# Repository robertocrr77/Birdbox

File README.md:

# Birdbox

DIY sensor-triggered ambience player inspired by the [Relaxound Birdybox](https://www.relaxound.com/birdybox-steamed-oak). An ESP32-C6 reads natural birdsong/forest ambience MP3 files from microSD and sends audio to a small speaker through an I2S amplifier. The intended finished device is battery powered; the current prototype is USB powered.

This README consolidates the project history, wiring, firmware behavior, setup, diagnostics, and remaining work. Active source is now V2 in [main/main.c](main/main.c), updated on 2026-11-17. The later V1 wiring/behavior sections describe the previously tested USB prototype and its archived source, not the active V2 image. Build results and physical tests are identified separately.

## Current status

### V2 motherboard routing

The saved two-layer PCB is routed. C1 moved closer to GPIO4. Signal traces
are 0.20 mm, the five supply nets use 0.60–0.80 mm traces, and B.Cu has a
ground pour with thermal reliefs. KiCad DRC and schematic parity reported
zero violations, zero unconnected pads, and zero schematic differences.
Assembly and electrical acceptance checks remain pending.

### Two-pole master switch

SW1 is one external latching DPDT pushbutton. Four individual wires solder
to two separate pairs of motherboard through-holes. Use the pin numbering
from the continuity-tested switch drawing.

| Motherboard pad | Net | Switch pin |
| --- | --- | --- |
| J5.1 | TP4056 protected OUT+ | 1 |
| J5.2 | XL63020 VIN | 2 |
| J7.1 | XL63020 VOUT | 4 |
| J7.2 | +3V3_AON | 5 |

ON closes 1–2 and 4–5. OFF connects 2–3 and 5–6 on the switch; pins 3 and 6
have no wires. Set SW1 to OFF when charging or flashing over the ESP32's USB
port. This opens both the battery feed and the connection between the
XL63020 output and the USB-powered 3.3 V rail. System ground remains common.
The switch's DC current rating and assembled behavior still need verification.

### V2 light sensing and deep sleep — 2026-11-17

Active firmware is `FW=birdbox-v2-light`. It implements motion wake, switched
peripheral power, a photoresistor night inhibit and RTC playlist retention.
**Do not flash onto unchanged V1 wiring:** PIR is now GPIO0; GPIO22 drives Q2.
GPIO4 reads light and GPIO14 excites the divider. Both added pins were checked
against the official Waveshare pinout image (`resources/esp32-c6-pinout.webp`).

Added R5 47k and C1 100n, plus J6 for a cabled bare LDR (R6, excluded from PCB).
J6 pin 1 is LIGHT_ADC_GPIO4; pin 2 is GND. Divider: GPIO14 -> 47k -> GPIO4
-> LDR -> GND, with 100n from GPIO4 to GND. GPIO14 is on while awake and held
LOW in sleep. Component footprints require comparison with actual parts.

User measurements: about 7k with lights on, 88k with hallway lighting; both
permit playback. Above nominal 100k for 3 seconds enters night; below 90k
returns to day. Initial calibrated ADC thresholds are 2245/2168 mV assuming
3.300 V excitation. These require physical calibration, particularly the
small margin between 88k and 90k. Darkness fades playback over about 200 ms.
The interrupted track is consumed. Night disables PIR wake and checks light
every 30 seconds; daylight return waits for new motion. Day idle also uses
deep sleep and periodic light checks. A held-HIGH PIR waits for LOW to rearm.
The six-track index survives deep sleep; cold reset starts at track 1.

ESP-IDF 5.3.1 ESP32-C6 build passed. Host C light-policy tests passed and KiCad
ERC reported zero errors/warnings. Exported schematic nets match PCB pads.
No flash or physical test was performed. Battery supply/module validation,
rail timing, back-power and sleep-current checks
are still required. See [V2 light circuit and behavior](resources/V2-Light-Sensor.md)
for complete wiring, calibration, test scope and acceptance checks.
Original source is retained in `main/main-v1.c.reference` and is not compiled.

### Q2 substitution — 2026-11-17

Q2 now uses PN2222A instead of BC547B in the schematic, project symbol library,
and unrouted PCB. The onsemi datasheet specifies 1=E, 2=B, 3=C (flat face
toward you, leads down: E-B-C). PCB pad 1 is GND, pad 2 is NPN_BASE,
and pad 3 is GATE_PULLDOWN. Resistor values are unchanged. Reference:
[PN2222/PN2222A datasheet](https://users.ece.utexas.edu/~valvano/Datasheets/PN2222-D.pdf).
The user's transistor is marked PN / 2222A / 6E with no identified manufacturer.
Reported diode readings were about 0.670 V forward on both base junctions and
OL reversed; this does not independently verify emitter/collector identity.
No firmware change or power-switch hardware test was performed.
KiCad 10 ERC after this substitution reported zero errors and zero warnings.
Exported Q2 net assignments match the PCB pads and both symbol definitions;
the board was unrouted at the time of the substitution.

### V2 KiCad schematic connections — 2026-11-15

The project schematic at `resources/schematics/schematics.kicad_sch` now uses
GPIO0 for AM312 OUT / HIGH-level deep-sleep wake and GPIO22 for active-HIGH
peripheral power enable. Both GPIOs were checked against the exact Waveshare
pinout image. GPIO5 remains the volume wiper input. ESP32 and PIR use
`+3V3_AON`. SD, amplifier and potentiometer use `+3V3_PERIPH` through the
through-hole PMOS/NPN reference circuit. These connections are a proposed V2
design and await physical verification.

The schematic includes Q1 NDP6020P, Q2 PN2222A, four axial resistors and the
J5/J7 solder pads for external master switch SW1. SW1 is excluded from the PCB.
User clarified that battery wires solder directly to the charger and speaker
wires directly to the amplifier before the modules are installed. These
connections bypass Motherboard copper. Added J3/J4 and amplifier symbol pins
8/9 were removed accordingly. Project-local symbols and library tables
accompany the schematic. Battery B- remains separate from protected system
GND. The PIR connector retains the user's pin assignment of
1=VCC, 2=OUT, 3=GND, requiring comparison with the actual AM312 markings.

KiCad 10 CLI export and ERC passed with zero errors and zero warnings. Exported
netlist checks passed for wake, control, volume, power rails and separation of
battery-negative from protected system ground. The rendered A3 drawing was
visually checked. U4 is the user-confirmed XL63020/TPS63020 module. The
previously reviewed footprint and STEP model are retained. Battery and speaker
connections are made directly on their
modules and require no Motherboard connector footprints.
Q1 is obsolete; the user has purchased NDP6020P parts, delivery pending. V2 firmware now implements sleep/wake and power sequencing; hardware validation remains pending.

V2 switching requirement: added components must be through-hole. The SMD
TPS22918 proposal is superseded by the discrete PMOS/NPN prototype circuit in
[resources/V2-Through-Hole-Power-Switch.md](resources/V2-Through-Hole-Power-Switch.md).
Exact reference-part connections and resistor values are documented; affordable
current-production local PMOS sourcing is still unresolved. NDP6020P is an
electrically suitable but obsolete reference, not a committed production part.
No new build, firmware change or physical validation has been performed.

V2 power-switching working plan uses the through-hole circuit described above.
Safe signal states and switched SD pull-ups are required to prevent back-power.
Regulator/module validation and startup-current measurements remain pending.

Earlier V2 regulator candidate: MakerMind RBS18349 XL63070/TPS63070 buck-boost
module (2–16 V listed input, default 5 V, solder-selectable output, 30 x 16 mm).
User photograph shows a 3V3 selector. Details and verification requirements
are in resources/V2-Motherboard.md. This is not yet an accepted replacement;
actual chip identity and module standby current remain unverified. Change
voltage selection only with power disconnected and measure 3.3 V before
connecting the system.

V2 PIR documentation reference: user supplied Adafruit 4871 via DigiKey.
[Manufacturer page](https://www.adafruit.com/product/4871) specifies 3–12 V
supply, 3.3 V digital output and pin markings minus=GND, O=OUT, plus=supply;
it links a datasheet. References are in resources/V2-Motherboard.md. Physical
equivalence to the retained ARCELI sensor has not been established.

V2 amplifier documentation: user supplied BerryBase ADA3006, the Adafruit
MAX98357A mono breakout (product 3006). Manufacturer schematic, fabrication
print, Eagle board files and 3D model are linked in resources/V2-Motherboard.md.
These are suitable sources for carrier footprint derivation; they do not
establish physical equivalence with the earlier Amazon amplifier module.

### V2 motherboard planning — 2026-11-15

V2 is a fresh PCB design. The existing firmware and prototype wiring below
remain the V1 hardware reference; V2 deep sleep and power switching are now implemented in source but not physically validated.

- User-confirmed construction: charger module, voltage regulator, SD reader,
  MAX98357A amplifier, potentiometer, and added circuitry will be soldered to
  the PCB, called the **Motherboard**. Retain the existing motion sensor.
- The external power switch and speaker connect to the Motherboard by cables.
  Battery connection and mounting must accommodate the actual battery.
- User-requested switch location: between battery output and voltage-regulator
  input. This is a design requirement, not yet a verified charging/protection
  circuit; final connections depend on the actual modules.
- Battery capacity: **3700 mAh**. Chemistry, nominal/maximum voltage, protection,
  dimensions, and exact battery/charger/regulator models are not recorded.
- Preserve six full tracks in sequence and existing cooldown behavior.
- Required V2 behavior: true deep sleep, sensor-HIGH wake-up, and switched
  peripheral power. The sensor must remain powered during motion-wait sleep.
- Activation frequency and runtime target are unspecified; do not require an
  estimated daily activation count to proceed with schematic planning.
- Housing files: `resources/BirdBox-Box.3mf` and
  `resources/BirdBox-Lid.3mf`. Both declare metres. Mesh bounding dimensions
  converted to millimetres: Box **106 × 152.163 × 28 mm**; Lid
  **106 × 152.163 × 27.5 mm**. These are individual-part outer bounding boxes,
  not usable PCB dimensions or the assembled enclosure height. Internal
  clearances, mounting, openings, and component interference still need review.

User-supplied component links and the initial schematic planning template are
recorded in [resources/V2-Motherboard.md](resources/V2-Motherboard.md).
The potentiometer is identified as Piher PT10MV10-103A2020-E-S; the retained
sensor is referenced by ARCELI listing B07RJQMD9G. Charger, regulator and other
module links are recorded, but their exact circuits and footprints remain
unverified. Battery capacity alone does not identify chemistry or voltage.
No V2 wiring or hardware test is established here.

Additional V2 SD reference supplied on 2026-11-15: BerryBase MSD-BO1,
[manufacturer listing](https://www.berrybase.de/micro-sd-card-reader-modul-mit-spi-schnittstelle-kompakt),
specified 3.3 V SPI and approximately 45 x 24 x 8 mm overall. A dimensioned
footprint and schematic were not found on that page. Identity with the existing
Amazon module and physical terminal geometry are not established.

V2 speaker mounting confirmed: glued into the housing lid, connected to the
Motherboard by two wires. User-supplied Tyenaza listing screenshot specifies
4 ohm, 3 W, approximately 40 x 40 x 20 mm. Allow assembly clearance beneath
the speaker and its terminals; no speaker footprint is required on the PCB.

Additional V2 charger reference: MakerMind RBS15537 TP4056 USB-C module,
[seller documentation](https://www.roboter-bausatz.de/p/tp4056-1a-lithium-ionen-lipo-lademodul-fuer-arduino-usb-c).
Listed for single-cell 4.2 V Li-ion/LiPo charging, up to 1 A, with protection;
overall 29 x 18 x 4 mm. Datasheet links and design limitations are recorded in
resources/V2-Motherboard.md. Identity with the existing Amazon module, exact
pad geometry and battery compatibility remain unverified. User clarified:
charge with the external power switch OFF; play with the switch ON and
charging disconnected. The switch is between the charger module's protected
load output and regulator input; the charger remains connected to the battery
while the system is OFF. Simultaneous charging/playback is not required. This
is a manual operating procedure, not an automatic electrical interlock.

Additional V2 regulator reference: MakerMind RBS16401,
[seller listing](https://www.roboter-bausatz.de/p/mini-spannungswandler-dc-1.8v-5v-auf-3.3v-fester-ausgang).
Specified 1.8–5 V input, fixed 3.3 V output, 100 mA continuous / 150 mA peak,
approximately 10.3 x 7.9 x 5.5 mm without pins, 2.54 mm pitch. This is not
accepted as the sole Motherboard supply: 0.33 W rated continuous output does
not establish adequate MCU/SD/amplifier playback capacity. Supply selection
and measured current/transient validation remain open. Identity with the
existing Amazon module has not been established.

**Regulator identification correction:** user clarified RBS16401 above is only
a similar example. The actual regulator's supplied listing specifies **4.5–7 V
input, 3.3 V output up to 800 mA**, approximately **1.2 V headroom**, module
size **8.6 x 12.33 mm**, and a power indicator. Do not apply the example's
100 mA rating to the actual hardware. User confirms current prototype operation;
actual current, voltage stability, thermal behavior and standby draw are unmeasured.
If the intended battery is a single cell charged to 4.2 V with the TP4056,
its output is below this regulator's listed minimum input even at full charge.
The requested battery-to-switch-to-regulator circuit therefore still needs
power-supply resolution; existing USB operation is not battery validation.

V2 battery identified by user-provided listing screenshot: **OCTelect LP103395
(103395), LiPo, 3.7 V nominal, 3700 mAh, 13.7 Wh**, described as having a JST
connector. Exact connector series/polarity, dimensions, protection and permitted
charge/discharge currents remain unverified. Listing pack quantity of two does
not define the device's cell count. Nominal single-cell voltage confirms that
the present regulator's 4.5 V minimum input is incompatible with the proposed
direct battery-fed topology within its listed specifications.

- Physical microSD MP3 playback has been confirmed by the user.
- Replacing minimp3 with Helix substantially improved sound, confirmed by the user. Timing tests support real-time playback on track 1 with the enlarged DMA buffer.
- Sensor-triggered playback and GPIO5 potentiometer volume control are implemented. Full integrated hardware verification remains pending.
- Startup waits for motion; it does not autoplay. One accepted trigger plays one complete track.
- Six tracks advance in order, then wrap to track 1. Triggers during playback/cooldown are ignored, never queued.
- The knob controls mute through a **40% digital amplitude ceiling**. This is not a percentage of speaker wattage or perceived loudness.
- The V1 prototype has no battery supply, charging, low-battery handling or deep sleep. Active V2 source now implements deep sleep; battery hardware and low-battery handling remain unresolved.

## Hardware needed

| Item | Specification / role | Status or limitation |
| --- | --- | --- |
| Microcontroller | Waveshare ESP32-C6-Zero | Project board; target `esp32c6` |
| Audio amplifier | MAX98357A I2S breakout | Current wiring powers VIN from 3V3 |
| Speaker | 4-ohm, 3 W | Connect only across amplifier speaker outputs |
| Storage interface | SPI microSD module with 3V3, CS, MOSI, CLK, MISO, GND | Existing module uses a 3.3 V supply; do not substitute an unverified module pinout |
| Storage | FAT32 microSD card | Holds all six MP3 files in its root |
| Motion sensor | Existing sensor referred to as PIR in firmware | Exact model and terminal arrangement are not documented; recorded connections are below |
| Volume control | 10 kOhm potentiometer | User-specified resistance; identify the actual wiper before connecting |
| Prototype supply/programming | USB data cable and computer running ESP-IDF | Current USB-powered setup |
| Interconnects | Suitable jumper wires and prototype connections | Keep SPI/audio wiring short and secure; share ground |
| Future power system | Battery, charger/protection, and suitable supply circuitry | Models, voltage conversion, connections, and runtime budget remain undecided |
| Final assembly | Enclosure and secure mounting | Final mechanical design is not documented |

Do not assume the DIY sensor behaves like the reference product's light-change detector. The reference product and its short sound duration are inspiration; this firmware plays each supplied file in full.

## V1 prototype wiring and power

Disconnect USB and any other power before changing connections. Use the board's **GPIO labels**, not header-position numbers. Board reference: Waveshare's exact [ESP32-C6-Zero Pinout Definition](https://docs.waveshare.com/ESP32-C6-Zero?variant=ESP32-C6-Zero#pinout-definition). The project records the GPIOs below as exposed board pins. Recheck that diagram before adapting the wiring to a different board; chip GPIO capability alone does not establish that a pin is exposed.

All modules share GND. The tables describe the recorded prototype connections, not a battery wiring design. Never apply 5 V to the SD module's 3V3 pin, potentiometer wiper, or ESP32 GPIO inputs. Verify the exact sensor's supply requirements and 3.3 V-compatible output before replacing it.

### Complete GPIO allocation

| ESP32-C6-Zero connection | Destination | Function |
| --- | --- | --- |
| GPIO1 | MAX98357A DIN | I2S audio data |
| GPIO2 | MAX98357A BCLK | I2S bit clock |
| GPIO3 | MAX98357A LRC / LRCLK / WS | I2S word select |
| GPIO5 | Potentiometer wiper | ADC1 channel 5, volume input |
| GPIO18 | SD CS | SPI chip select |
| GPIO19 | SD MOSI | SPI data to card |
| GPIO20 | SD CLK | SPI clock |
| GPIO21 | SD MISO | SPI data from card |
| GPIO22 | Sensor OUT | Motion input, rising edge |
| 3V3 | Amplifier VIN, SD 3V3, recorded sensor VCC, one potentiometer end | Prototype 3.3 V rail |
| GND | Amplifier GND, SD GND, sensor GND, other potentiometer end | Common ground |

### MAX98357A and speaker

| Amplifier terminal | Connection |
| --- | --- |
| VIN | ESP32 3V3 |
| GND | ESP32 GND |
| DIN | GPIO1 |
| BCLK | GPIO2 |
| LRC / LRCLK / WS | GPIO3 |
| Speaker + and speaker - | The two speaker wires, one to each output |
| GAIN | Left unconnected in the prototype |
| SD / EN, if present | Must not be held LOW; check the actual breakout's enable arrangement |

Neither speaker terminal connects to GND: these are differential amplifier outputs. Typical MAX98357A breakouts can operate with SD/EN unconnected, but the exact breakout circuitry has not been documented here. No MCLK connection is used.

### SPI microSD module

| Module terminal | ESP32 connection |
| --- | --- |
| 3V3 | 3V3 only |
| CS | GPIO18 |
| MOSI | GPIO19 |
| CLK | GPIO20 |
| MISO | GPIO21 |
| GND | GND |

Firmware limits SPI to 4 MHz for this jumper-wire prototype. Card mounting never automatically formats the card. Required pull-ups depend on the actual module; inspect its circuitry if mounting fails.

### Motion sensor

Recorded wiring: **VCC -> 3V3, GND -> GND, OUT -> GPIO22**. Its exact model, physical pin order, warm-up time, sensitivity, hold time, and retrigger settings are unknown. Identify terminals from the actual sensor rather than assuming a layout from a photograph.

GPIO22 is configured as an input with neither internal pull-up nor pull-down. The sensor must provide a defined, compatible logic signal. Firmware polls every 20 ms; this is not an interrupt input and very short pulses may be missed.

### 10 kOhm volume potentiometer

Connect the **verified wiper to GPIO5**, and the two resistance-track ends to **3V3 and GND**. Swap the ends to reverse rotation. The earlier stock photo did not establish the actual terminal arrangement; do not infer it here. With power disconnected, the end-to-end resistance should stay approximately constant while resistance from the wiper to either end changes as the shaft turns.

GPIO0 was not a previously implemented volume input. Use GPIO5 / ADC1 channel 5.

GPIO5 also serves as a reset-time SDIO clock-edge strapping pin and external JTAG pin. This project uses SPI storage on GPIO18-21 and USB/serial flashing, not SDIO or external JTAG. **Boot/reset must still be tested at both knob endpoints.** Physical knob behavior has not been established by a firmware build.

## Prepare the microSD card

1. Back up existing card contents before any formatting. Use FAT32; firmware does not format cards for you.
2. Copy the six files from [sdcard/](sdcard/) directly to the card root:

   ```text
   1_mono.mp3
   2_mono.mp3
   3_mono.mp3
   4_mono.mp3
   5_mono.mp3
   6_mono.mp3
   ```

   For example, `E:\1_mono.mp3`, not `E:\sdcard\1_mono.mp3`.
3. Safely eject the card and insert it with the prototype powered off.
4. Connect power, flash the firmware if needed, and check the serial monitor for successful mounting.

The recordings were converted to mono; requested ambience includes birdsong, a nearby stream, and background insects. Replacement files must be actual MPEG Layer III MP3 files with the same names. Renaming a WAV file does not convert it. The implementation accepts mono/stereo decoded frames at 8-48 kHz with 16-bit output; stereo is averaged to mono and duplicated into both I2S channels. Free-bitrate MP3 files are rejected. Files play for their own duration, with no fixed 20-second cutoff.

The internal mount path is `/sdcard`; that directory name does not belong on the physical card. Supplied assets total approximately 11.7 MB. Audio-content redistribution rights are not established by the decoder license.

## V1 firmware behavior (archived source)

### Startup and trigger sequence

1. Startup identifies the firmware as `FW=pot-gpio5-v1`, with build date/time, decoder-debug setting, and maximum volume.
2. Volume monitoring and GPIO22 sensor monitoring start. Digital gain initially stays muted until a successful ADC read.
3. With audio enabled, firmware mounts the SD card, initializes I2S, and writes two seconds of silence before announcing `Ready for motion; next track 1/6`.
4. A newly observed LOW-to-HIGH transition while ready consumes the readiness token and starts one complete track.
5. After success, firmware writes three seconds of silence. After failure, it logs the failed file and writes five seconds of silence. This also flushes queued audio.
6. It advances the playlist index and waits for another new rising edge. Track 6 wraps to track 1; reset restarts the index at track 1.

A held HIGH does not retrigger. Initial HIGH at sensor initialization is not itself counted as an edge. Motion while initializing, playing, or cooling down is logged and discarded. It does not restart a file or queue another. Startup sensor settling may still create subsequent rising edges.

A failed file consumes that accepted trigger and advances the index after the failure cooldown; the next file requires a new trigger. If SD mounting fails, the player task stops and sensor monitoring continues without playback readiness. Correct the card problem and reset to retry.

### Knob processing

Every 50 ms the volume task averages eight 12-bit ADC readings, then smooths the result using `(3 * previous + new) / 4`. ADC attenuation is configured as `ADC_ATTEN_DB_12`. Filtered readings at or below 40 map to mute; readings at or above 4000 map to the configured maximum. Intermediate readings map linearly to digital gain.

Playback ramps from the previous gain to the new gain across each decoded frame to reduce clicks. Each track begins with its previous gain set to zero. An ADC read failure retains the last gain and logs a warning; failure before any successful read leaves gain muted.

### Configuration in archived main/main-v1.c.reference

| Setting | Saved value | Purpose |
| --- | --- | --- |
| `ENABLE_AUDIO_PLAYBACK` | `1` | Motion-triggered playback; `0` retains sensor monitoring and the volume task without starting the player |
| `VOLUME_PERCENT` | `40` | Maximum digital amplitude permitted by the knob, valid range 0-100 |
| `ENABLE_DECODER_DEBUG` | `0` | Enables decoder startup/MP3 format and timing messages when set to 1 |
| `ENABLE_VOLUME_DEBUG` | `0` | Enables GPIO5 raw, filtered, and gain logging approximately once per second when set to 1 |
| `PIR_POLL_MS` | `20` | Sensor polling interval |
| `VOLUME_POLL_MS` | `50` | Volume update interval |
| `VOLUME_ADC_MIN` / `VOLUME_ADC_MAX` | `40` / `4000` | Knob endpoint thresholds |
| `DMA_DESCRIPTORS` / `DMA_FRAMES` | `12` / `480` | I2S DMA buffer configuration |

Rebuild and flash after editing these constants. Sensor events, operational playback messages, warnings, and errors remain visible with decoder debug disabled. Older notes mentioning fixed 20% volume or `ENABLE_VOLUME_DEBUG=1` describe earlier states and are superseded by the saved values above.

## Build, flash, and monitor

Active workspace: `C:\Users\Familie_Ruvalcaba\Documents\Projects\Birdbox`, **not BirdboxVS**. Open the folder containing this README and `CMakeLists.txt`.

This is a native **ESP-IDF 5.3.1** project, target **ESP32-C6**. It does not require Arduino or Arduino Audio Tools. The bundled Helix component is built locally. Main component dependencies are ESP ADC, GPIO, I2S, SPI, FATFS, SDMMC, Helix, and ESP timer.

In VS Code with the ESP-IDF extension:

1. Select the ESP-IDF installation and run **ESP-IDF: Set Espressif Device Target** -> `esp32c6` when configuring a fresh checkout.
2. Run **ESP-IDF: Build your project**.
3. Connect a USB data cable and run **ESP-IDF: Select Port to Use**.
4. Run **ESP-IDF: Flash your project**, selecting UART/serial when asked. The board's USB Serial/JTAG connection is available through its serial COM port.
5. Run **ESP-IDF: Monitor your device**.

Alternatively, in a terminal with ESP-IDF activated:

```powershell
idf.py set-target esp32c6
idf.py build
idf.py -p COM3 flash monitor
```

Use `set-target` for initial configuration or a target change; it can regenerate build configuration. Replace `COM3` with the actual port. The saved VS Code settings currently select COM3 and UART flashing; these are machine-specific settings, not a guaranteed port assignment. Exit the monitor with **Ctrl+]**. Close other serial monitors before flashing. If download mode is needed, hold BOOT, press/release RESET, then release BOOT and retry.

`sdkconfig.defaults` sets the ESP32-C6 target and USB Serial/JTAG console. Local `sdkconfig` and generated `build/` are ignored by Git. A fresh checkout needs a build to regenerate compiler/IntelliSense artifacts.

Before saving `main/main.c`, reconcile any unsaved editor buffer with the disk version. An older buffer previously overwrote the restored potentiometer implementation. Verify the startup firmware marker and build timestamp after flashing to confirm which firmware is running.

## V1 expected serial output (archived source)

The exact timestamps and interleaving depend on task scheduling. Typical messages include:

```text
FW=pot-gpio5-v1 built ...; decoder_debug=0; max_volume=40%
Motion playback enabled=1; volume=40%
10k potentiometer on GPIO5 (ADC1_CH5); range mute to 40%
Monitoring GPIO22; initial level=...
SD: CS=18 MOSI=19 CLK=20 MISO=21
SD mounted (card contents are never auto-formatted)
Audio: DIN=1 BCLK=2 LRC=3. Preparing motion-triggered playback.
Ready for motion; next track 1/6
Motion detected: trigger #1 (GPIO22 LOW -> HIGH)
Motion accepted: track 1/6
Playing /sdcard/1_mono.mp3 (potentiometer volume; maximum 40%)
Playback finished (... frames)
Ready for motion; next track 2/6
```

Busy events produce `Trigger ignored: audio is busy, cooling down, or not ready`. With decoder debugging disabled, absence of MP3 format or `audio_diag` lines is expected. With volume debugging disabled, absence of periodic raw knob readings is expected.

## Audio repair history and measured performance

The original mono MP3 sounded natural on the PC but metallic/robotic on the ESP32-C6. On-device minimp3 measurements showed roughly 34.3-34.9 ms decoding for frames containing only 24 ms of audio, and about 40 ms total preparation/pacing. Sustained starvation explained the symptom; it was not sufficient evidence of an amplifier defect.

The repair replaced minimp3 with **Helix fixed-point MP3 decoding**, batched compressed SD reads into a 16,384-byte input buffer, and removed the artificial delay after each frame. Blocking I2S writes now pace playback. The user confirmed much better sound. Helix measured approximately **2.3 ms decoding per 24 ms audio frame**, about 15 times faster than the measured previous decoder.

Occasional SD reads of approximately 37-39 ms still exceeded the former 30 ms DMA capacity. Buffering was increased to **12 x 480 stereo frames**, consuming 23,040 bytes of 16-bit stereo sample memory and representing **120 ms at 48 kHz**. Capacity in time changes with sample rate.

A track-1 hardware retest over approximately 40 seconds showed around 209 decoded frames per five-second reporting window, about 2.3 ms mean decode time, approximately 41 ms maximum feed gaps, and zero feed gaps exceeding configured DMA capacity. This supports real-time throughput for that test; it does not establish all-track reliability or directly count I2S underruns.

### Decoder diagnostics

Set `ENABLE_DECODER_DEBUG=1`, rebuild, flash, then capture the decoder startup, MP3 format, and at least three pairs of `audio_diag` messages during playback. Reports occur about every five seconds and at track end when frames have been collected.

| Metric | Meaning |
| --- | --- |
| `audio/frame` | Audio duration represented by a decoded frame, in microseconds |
| `SD avg/max` | Compressed-read time per reporting window |
| `decode avg/max` | Decoder time per reporting window |
| `prepare+pace avg` | Preparation time before I2S write plus explicit pacing delay; blocking I2S writes are excluded, explicit delay is now zero |
| `over-budget` | Frames whose preparation/pacing took longer than their audio duration |
| `max feed gap` | Longest measured interval between a completed write and the next write starting |
| `gaps exceeding DMA capacity` | Feed gaps exceeding the maximum configured buffer duration at the active sample rate |

These timing indicators are **not hardware underrun counters**. The actual queue may be partially filled, so zero long gaps does not prove zero underruns. Logging itself adds overhead. Restore debug to 0 after diagnosis if the extra output is no longer needed.

## Troubleshooting

| Symptom / message | Checks and recovery |
| --- | --- |
| `SD mount failed` | Power off; check FAT32, 3V3, common ground, GPIO18-21 wiring, card seating, and module pull-ups. Correct the cause and reset; there is no automatic remount loop. |
| `Cannot open /sdcard/...` | Check exact numbered filename and card root. Failure advances the index after five seconds; another trigger is required. |
| `No playable MP3 frames`, decode error, unsupported or truncated MP3 | Replace/re-encode the affected file as supported Layer III MP3. Check for damaged card data. |
| Playback messages but no sound | Turn the knob up; check GPIO5 wiper/end wiring and amplifier enable, DIN/BCLK/LRC, speaker terminals, and common ground with power disconnected. |
| Knob has no effect | Temporarily enable volume debugging, rebuild/flash, and check raw/filtered changes. Confirm GPIO5 rather than GPIO0 and identify the actual wiper. |
| Knob does not reach mute or maximum | Inspect debug readings at both ends, then tune ADC thresholds only from measured values. |
| `ADC read failed` | Firmware keeps the previous gain. Check volume input wiring and ADC setup; initial gain remains mute if no read succeeds. |
| Motion logs but no playback | Check `ENABLE_AUDIO_PLAYBACK`, successful SD mounting, and `Ready for motion`. Events during busy/cooldown/startup are intentionally ignored. |
| Held sensor HIGH does not start another track | Expected: input must return LOW and then rise HIGH after readiness. |
| Unexpected startup motion | Allow the actual sensor to settle; its warm-up behavior has not been characterized. |
| Metallic, interrupted, or stuttering sound | Enable decoder diagnostics; compare preparation and feed gaps with audio duration and DMA capacity. Check card/wiring as well as decoding performance. |
| Flashing fails or old behavior remains | Confirm correct workspace, target and COM port, close competing monitors, rebuild/flash, and inspect startup marker/build time. Reconcile unsaved editor content. |
| Boot changes with knob position | Record behavior at each endpoint and investigate GPIO5's reset-time strapping role before treating the assembly as validated. |

## Work completed and validation record

| Stage | Work / evidence | Limit |
| --- | --- | --- |
| Initial audio prototype | ESP32-C6-Zero, I2S amplifier/speaker, and SPI SD wiring documented; native ESP-IDF MP3 player implemented | USB-powered prototype |
| 2026-11-01 build and desktop checks | ESP-IDF 5.3.1 ESP32-C6 build passed, with about 73% of the existing 1 MB app partition free; FFmpeg decoded a supplied MP3 without errors (32 kHz, mono, 96 kbps, about 30.06 s including padding) | Historical check of a supplied file, not metadata/validation for all six current assets |
| Physical SD playback | User confirmed playback from microSD | Does not by itself validate every later change |
| Six-track playlist | Numbered mono assets added; sequence 1-6 then 1 | Full current playlist test remains pending |
| Decoder repair | Helix replaced minimp3; 2026-11-01 build passed with about 72% app partition free; user confirmed improved sound | Historical size figures, not a new build measurement |
| DMA repair | Buffer enlarged after measured SD stalls; track-1 timing retest supported real-time throughput | Approximately 40-second sample; not all tracks or direct underrun measurement |
| Motion mode | GPIO22 rising-edge monitoring, one-track triggers, ignored busy events, and success/failure cooldown implemented; build reported passed | Sensor-to-audio hardware retest pending |
| 2026-11-08 volume control and repair | GPIO5 ADC knob, smoothing, gain ramp, 40% ceiling and firmware marker restored after saved source reverted to fixed gain/unconditional diagnostics | Physical endpoint, boot, and playback tests pending |
| 2026-11-10 documentation review | Consolidated README against saved source; both debug flags currently 0 | Documentation-only review; no new build, flash, or hardware test performed |

Obsolete Arduino sketches, unused minimp3 sources, synthetic test audio, and temporary audio tooling were removed during earlier cleanup. No firmware source is changed by this documentation update.

### Hardware acceptance checklist

- [ ] Flash the intended build and confirm firmware marker, build time, and configuration.
- [ ] Confirm startup stays silent and waits for a new sensor edge after readiness.
- [ ] Trigger all six tracks individually; confirm full playback, order, and wrap to track 1.
- [ ] Confirm held HIGH, playback-time motion, and cooldown motion do not queue/restart tracks.
- [ ] Confirm three-second success cooldown and five-second failed-file behavior with a controlled missing-file test on a backed-up card.
- [ ] Test SD mount failure and recovery by correction/reset.
- [ ] Test knob mute, full permitted volume, smooth changes during playback, and usable travel.
- [ ] Reset/boot with the knob at both endpoints and intermediate positions.
- [ ] Listen through every complete track and collect timing diagnostics if interruptions occur.
- [ ] Characterize the actual sensor's warm-up, range, output levels, and retrigger settings.

## Remaining battery and enclosure work

Select and document the exact battery, charger/protection, and any voltage regulation before assigning connections. Establish a power budget from measured idle/playback current, check supply behavior during SD/audio load, and define safe power switching and charging behavior. Runtime cannot be calculated reliably from the available information. No battery connection or charging method is approved by the existing USB wiring tables.

Decide whether low-power sleep, amplifier shutdown, or other idle-power reductions are required for the runtime goal. Then document the final enclosure, speaker mounting, sensor placement, card/USB access, and secured wiring. These are future design tasks rather than implemented features.

## Repository map and decoder provenance

| Path | Purpose |
| --- | --- |
| [main/main.c](main/main.c) | Active V2 controller, player, power sequencing and sleep |
| [main/v2_sensing.h](main/v2_sensing.h) | ADC sensing, volume, safe interfaces and wake configuration |
| [main/light_policy.h](main/light_policy.h) | Light thresholds, hysteresis and dark confirmation |
| `main/main-v1.c.reference` | Archived V1 source, excluded from compilation |
| [main/CMakeLists.txt](main/CMakeLists.txt) | Main component dependencies |
| [components/helix/](components/helix/) | Vendored fixed-point MP3 decoder, local build integration, original licenses |
| [sdcard/](sdcard/) | Six numbered mono MP3 assets to copy to the card root |
| `.vscode/` | Local ESP-IDF and IntelliSense configuration |
| `sdkconfig.defaults` | Default target/console configuration |
| `CMakeLists.txt` | ESP-IDF project entry (`birdbox_audio_test`, retained project name) |
| `build/`, `sdkconfig` | Generated/local configuration; ignored by Git |
| [AGENTS.md](AGENTS.md) | Project context and working instructions |

Helix MP3 C sources were vendored from [pschatzmann/codec-helix](https://github.com/pschatzmann/codec-helix/tree/f6e55a307c7577c5e3dfe1bf424a61075235fa08), commit `f6e55a307c7577c5e3dfe1bf424a61075235fa08`, retrieved 2026-11-01. Original headers and `LICENSE.txt`, `RPSL.txt`, and `RCSL.txt` are retained under `components/helix/libhelix-mp3`. Local memory glue supplies malloc/free; component compilation uses `-O2` and `-fwrapv`, with the upstream RISC-V integer multiply path. Review those license files before redistribution. The component's own historical README predates the successful hardware timing retest described above.

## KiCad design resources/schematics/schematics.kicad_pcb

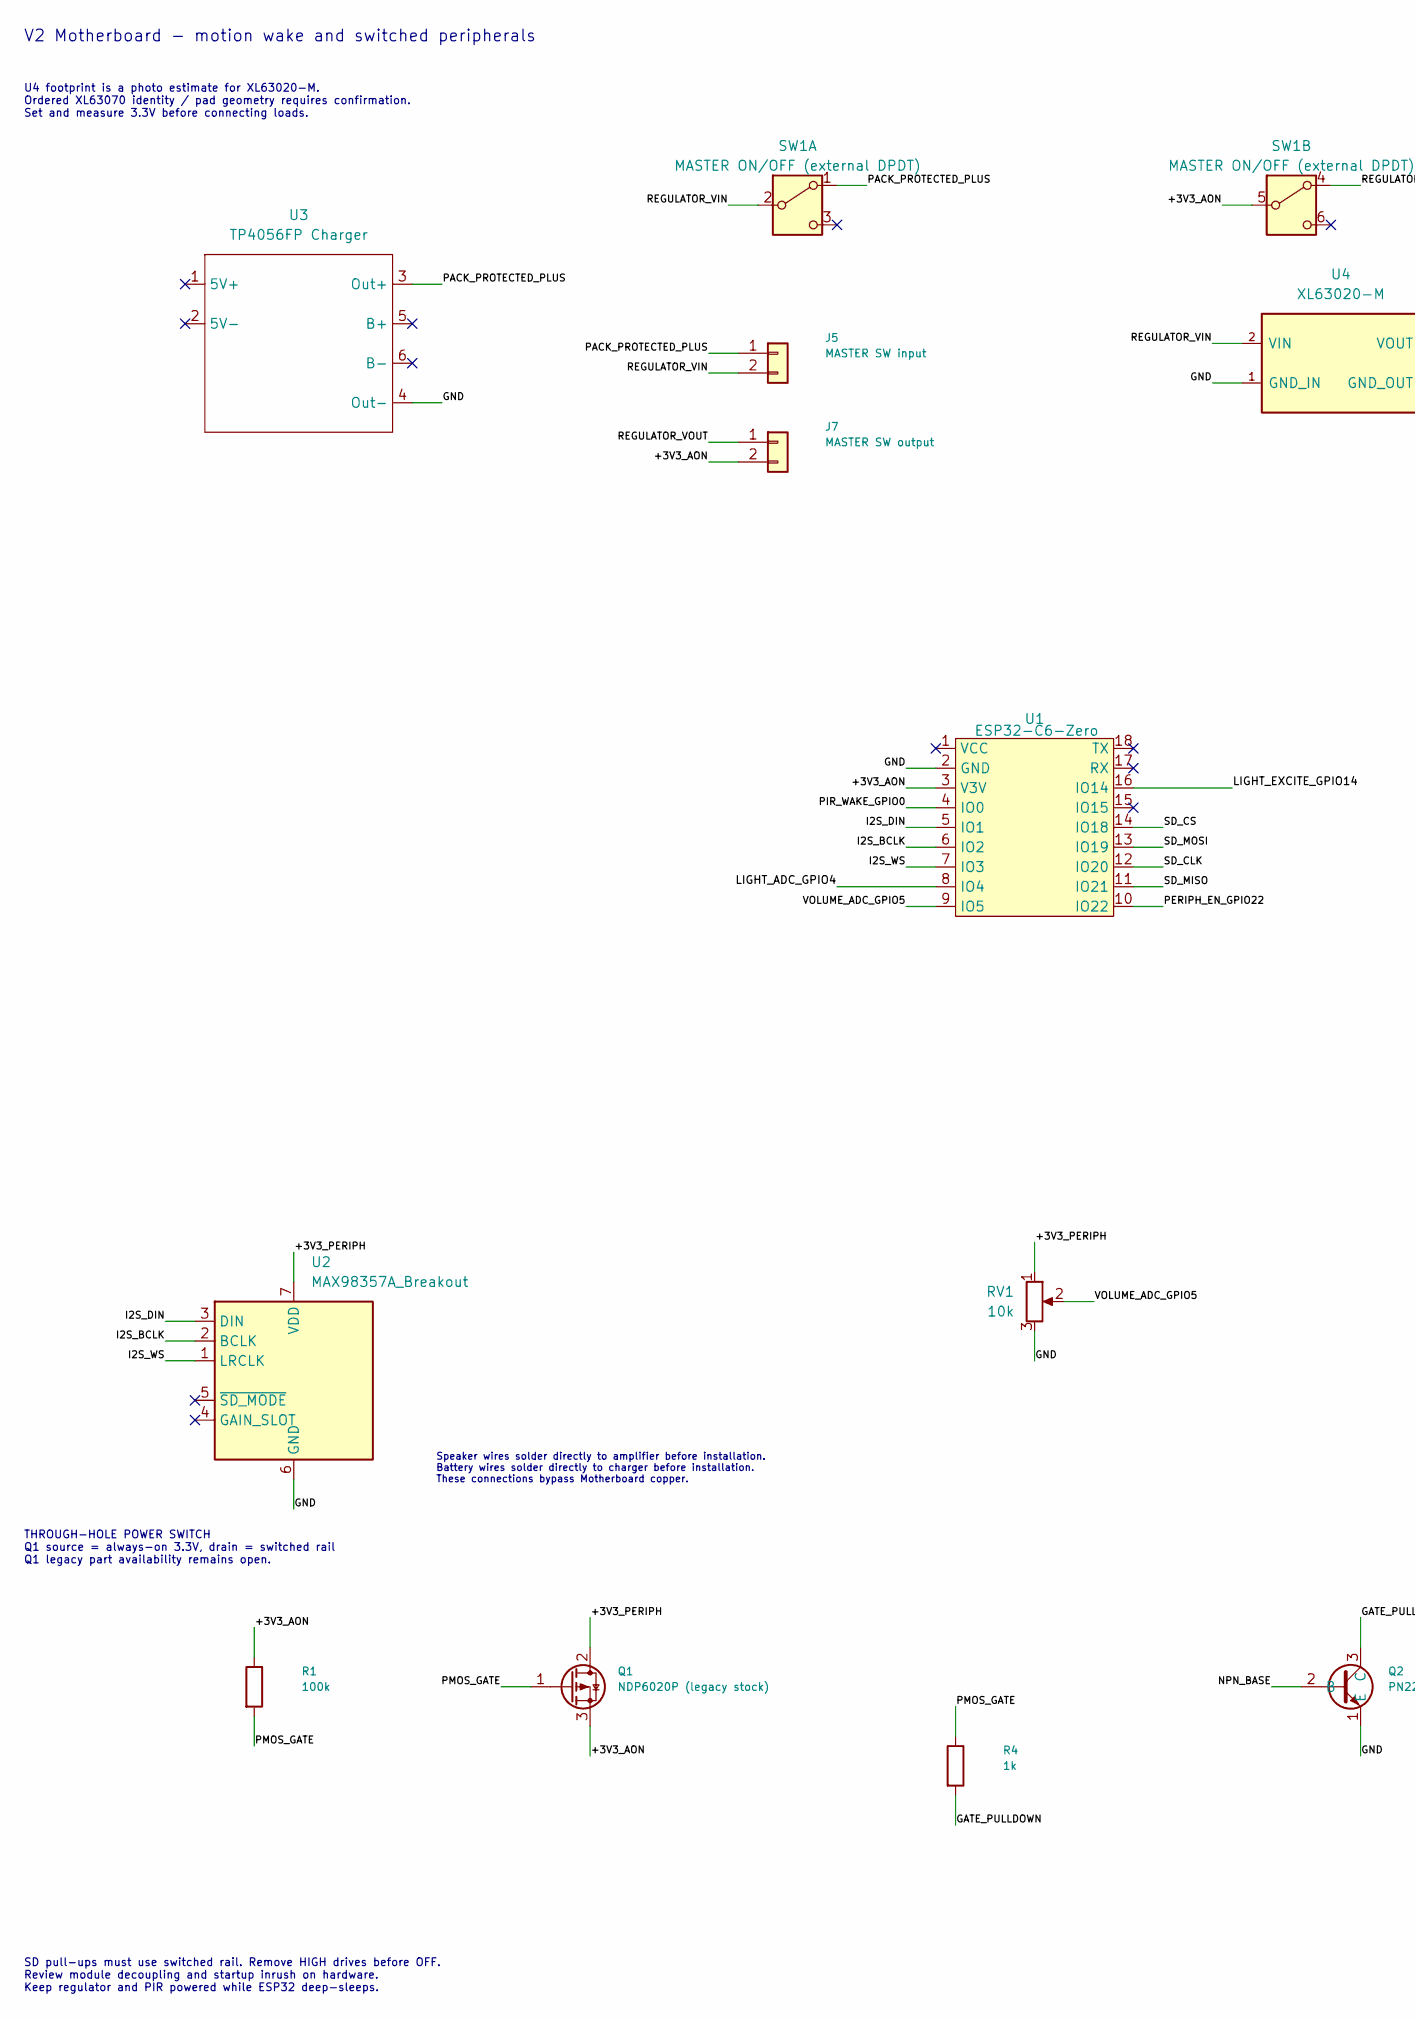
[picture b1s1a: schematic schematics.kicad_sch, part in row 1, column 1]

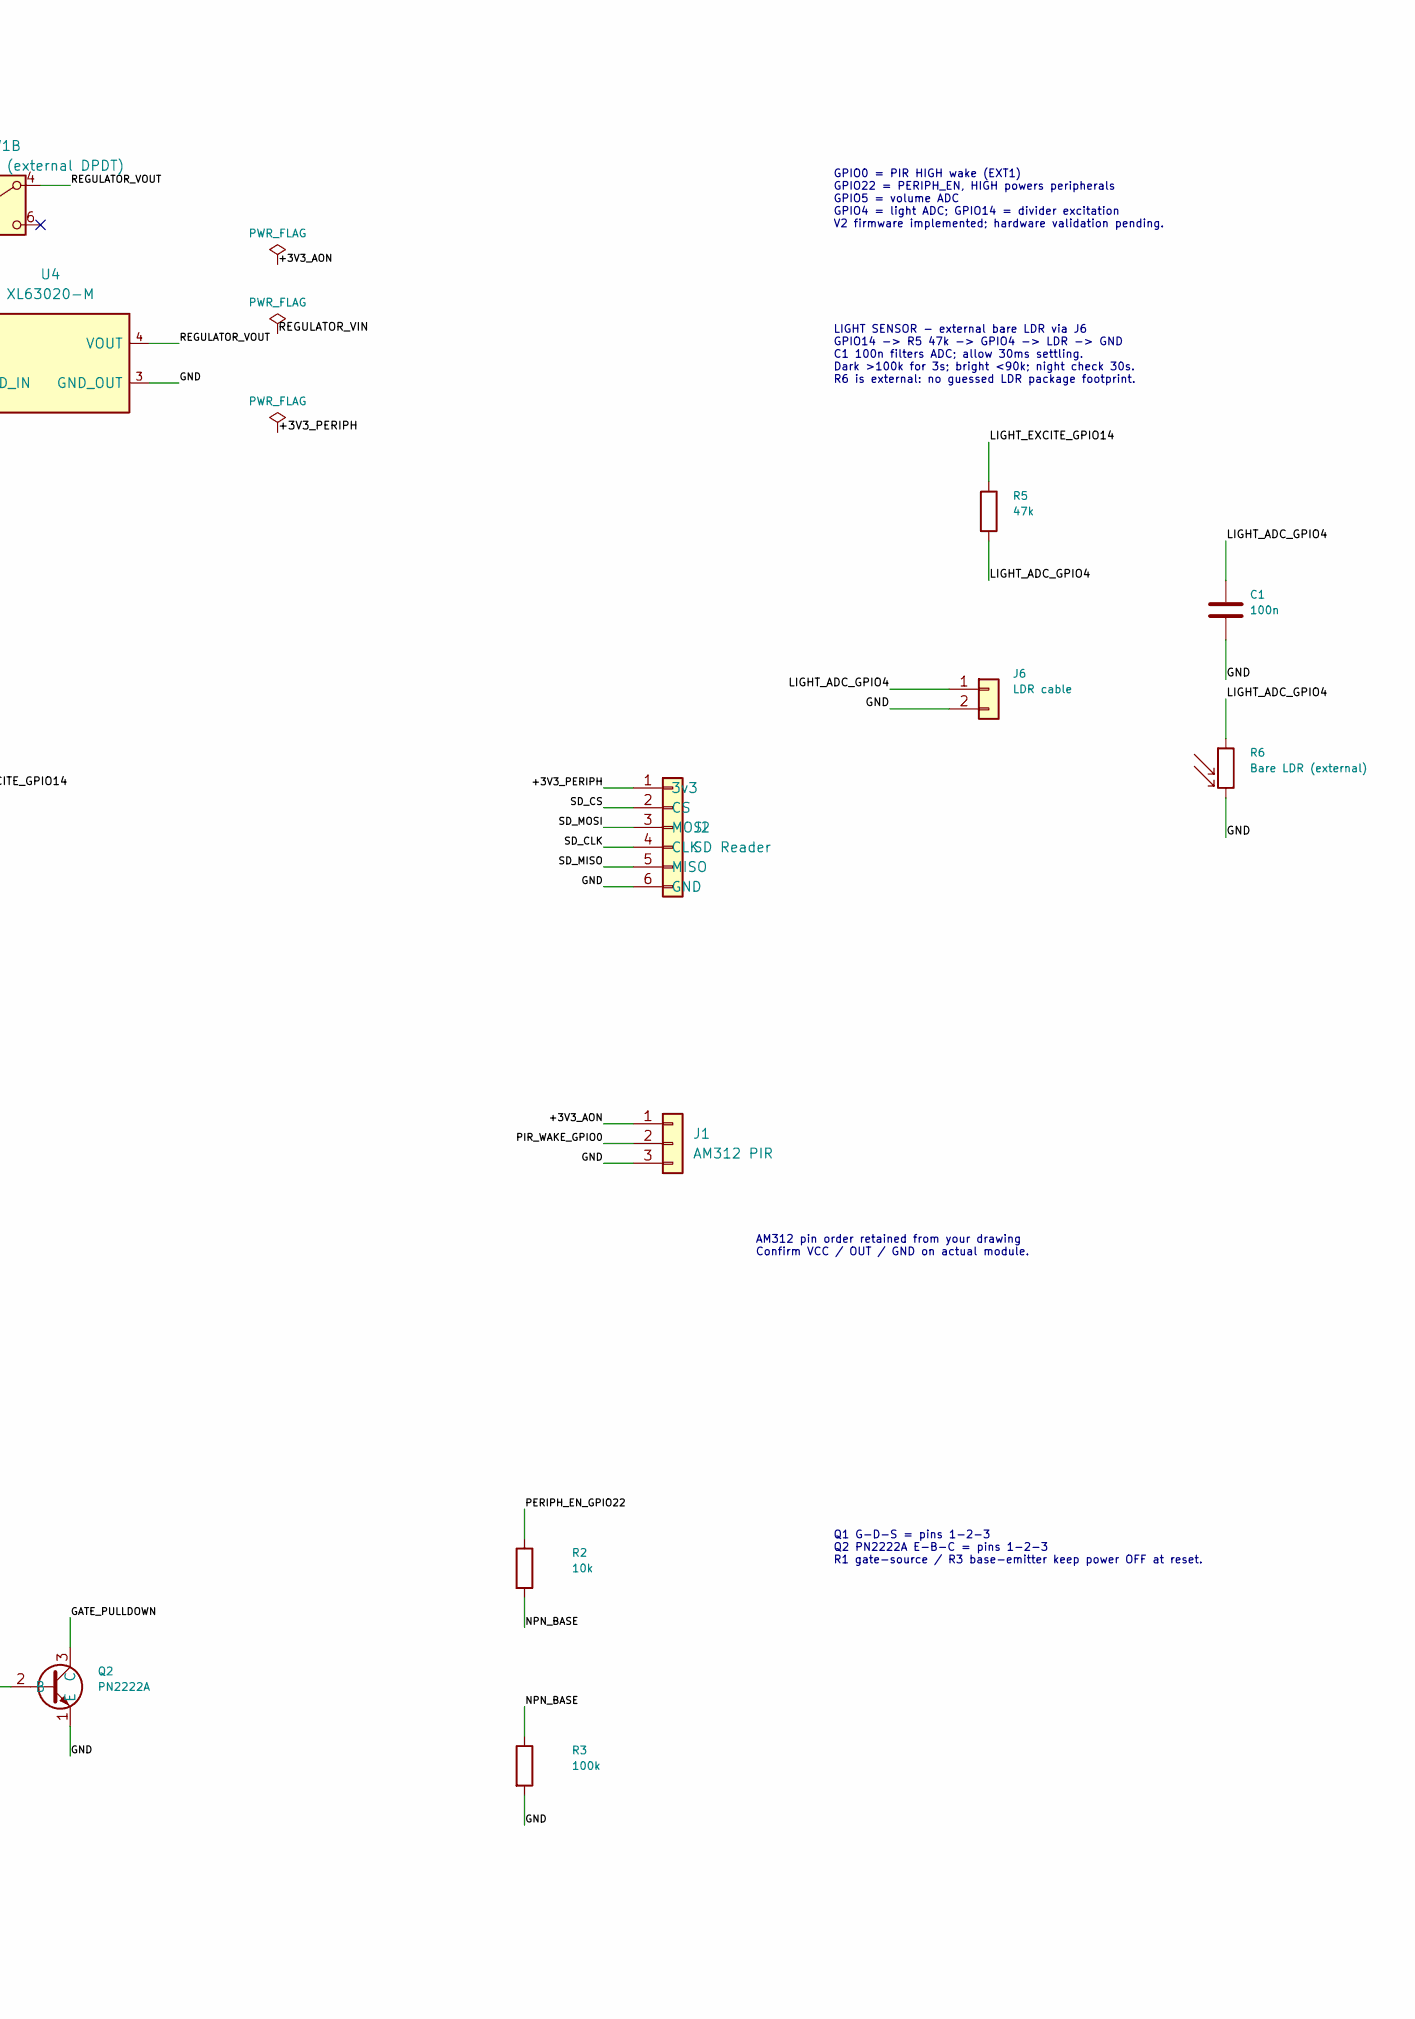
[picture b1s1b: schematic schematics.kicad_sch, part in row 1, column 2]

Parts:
C1: 100n; C_Disc_D5.0mm_W2.5mm_P5.00mm
J1: AM312 PIR; PinHeader_1x03_P2.54mm_Vertical
J2: SD Reader; PinHeader_1x06_P2.54mm_Vertical
J5: MASTER SW input; PinHeader_1x02_P2.54mm_Vertical
J6: LDR cable; PinHeader_1x02_P2.54mm_Vertical
J7: MASTER SW output; PinHeader_1x02_P2.54mm_Vertical
Q1: NDP6020P (legacy stock); TO-220-3_Vertical
Q2: PN2222A; TO-92_Inline
R1, R3: 100k; R_Axial_DIN0207_L6.3mm_D2.5mm_P10.16mm_Horizontal
R2: 10k; R_Axial_DIN0207_L6.3mm_D2.5mm_P10.16mm_Horizontal
R4: 1k; R_Axial_DIN0207_L6.3mm_D2.5mm_P10.16mm_Horizontal
R5: 47k; R_Axial_DIN0207_L6.3mm_D2.5mm_P7.62mm_Horizontal
R6: Bare LDR (external)
RV1: 10k; Potentiometer_Piher_PT-10-V10_Vertical_Hole
SW1: MASTER ON/OFF (external DPDT)
U1: ESP32-C6-Zero; Waveshare-ESP32-C6-Zero_THT
U2: MAX98357A_Breakout; MAX98357A breakout
U3: TP4056FP Charger; TP4056-18650
U4: XL63020-M; XL63020-M_PhotoEstimate

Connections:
/+3V3_AON: J1.1, J7.2, Q1.3 (S), R1.1, SW1.5 (B), U1.3 (V3V)
/+3V3_PERIPH: J2.1 (3v3), Q1.2 (D), RV1.1, U2.7 (VDD)
/GATE_PULLDOWN: Q2.3 (C), R4.2
/GND: C1.2, J1.3, J2.6 (GND), J6.2, Q2.1 (E), R3.2, R6.2, RV1.3, U1.2 (GND), U2.6 (GND), U3.4 (Out-), U4.1 (GND_IN), U4.3 (GND_OUT)
/I2S_BCLK: U1.6 (IO2), U2.2 (BCLK)
/I2S_DIN: U1.5 (IO1), U2.3 (DIN)
/I2S_WS: U1.7 (IO3), U2.1 (LRCLK)
/LIGHT_ADC_GPIO4: C1.1, J6.1, R5.2, R6.1, U1.8 (IO4)
/LIGHT_EXCITE_GPIO14: R5.1, U1.16 (IO14)
/NPN_BASE: Q2.2 (B), R2.2, R3.1
/PACK_PROTECTED_PLUS: J5.1, SW1.1 (A), U3.3 (Out+)
/PERIPH_EN_GPIO22: R2.1, U1.10 (IO22)
/PIR_WAKE_GPIO0: J1.2, U1.4 (IO0)
/PMOS_GATE: Q1.1 (G), R1.2, R4.1
/REGULATOR_VIN: J5.2, SW1.2 (B), U4.2 (VIN)
/REGULATOR_VOUT: J7.1, SW1.4 (A), U4.4 (VOUT)
/SD_CLK: J2.4 (CLK), U1.12 (IO20)
/SD_CS: J2.2 (CS), U1.14 (IO18)
/SD_MISO: J2.5 (MISO), U1.11 (IO21)
/SD_MOSI: J2.3 (MOSI), U1.13 (IO19)
/VOLUME_ADC_GPIO5: RV1.2, U1.9 (IO5)

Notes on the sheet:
LIGHT SENSOR - external bare LDR via J6 GPIO14 -> R5 47k -> GPIO4 -> LDR -> GND C1 100n filters ADC; allow 30ms settling. Dark >100k for 3s; bright <90k; night check 30s. R6 is external: no guessed LDR package footprint.
SD pull-ups must use switched rail. Remove HIGH drives before OFF. Review module decoupling and startup inrush on hardware. Keep regulator and PIR powered while ESP32 deep-sleeps.
AM312 pin order retained from your drawing Confirm VCC / OUT / GND on actual module.
Q1 G-D-S = pins 1-2-3 Q2 PN2222A E-B-C = pins 1-2-3 R1 gate-source / R3 base-emitter keep power OFF at reset.
V2 Motherboard - motion wake and switched peripherals
Speaker wires solder directly to amplifier before installation. Battery wires solder directly to charger before installation. These connections bypass Motherboard copper.
U4 footprint is a photo estimate for XL63020-M. Ordered XL63070 identity / pad geometry requires confirmation. Set and measure 3.3V before connecting loads.
GPIO0 = PIR HIGH wake (EXT1) GPIO22 = PERIPH_EN, HIGH powers peripherals GPIO5 = volume ADC GPIO4 = light ADC; GPIO14 = divider excitation V2 firmware implemented; hardware validation pending.
THROUGH-HOLE POWER SWITCH Q1 source = always-on 3.3V, drain = switched rail Q1 legacy part availability remains open.

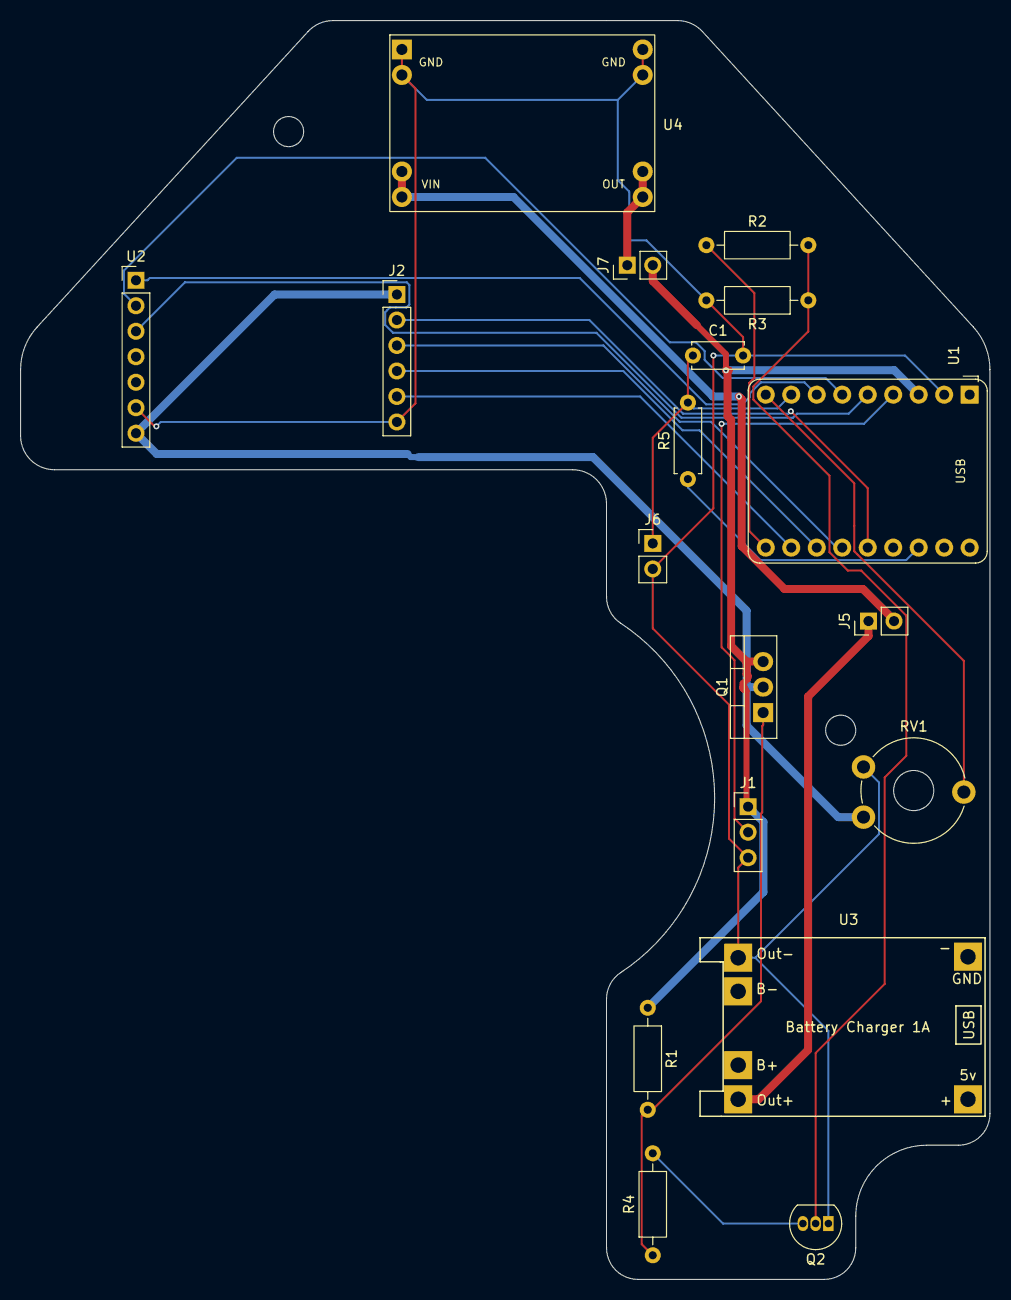
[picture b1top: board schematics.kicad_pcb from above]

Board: 2 copper layers, 96.6 x 125.4 mm, 18 parts (0 on the bottom side), 21 nets.

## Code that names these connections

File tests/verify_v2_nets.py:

"""Run with KiCad's Python after exporting a KiCad XML netlist to build/v2-light.net."""
from pathlib import Path
import xml.etree.ElementTree as ET
import pcbnew

xml = ET.parse('build/v2-light.net').getroot()
nets = {n.attrib['name']: {(p.attrib['ref'], p.attrib['pin']) for p in n.findall('node')}
        for n in xml.find('nets')}
assert nets['/LIGHT_ADC_GPIO4'] == {('U1','8'),('R5','2'),('C1','1'),('J6','1'),('R6','1')}
assert nets['/LIGHT_EXCITE_GPIO14'] == {('U1','16'),('R5','1')}
assert {('C1','2'),('J6','2'),('R6','2'),('Q2','1')} <= nets['/GND']
assert ('U1','4') in nets['/PIR_WAKE_GPIO0']
assert ('U1','10') in nets['/PERIPH_EN_GPIO22']
assert ('U1','9') in nets['/VOLUME_ADC_GPIO5']
assert ('Q2','3') in nets['/GATE_PULLDOWN']
assert {('U3', '3'), ('J5', '1'), ('SW1', '1')} == nets['/PACK_PROTECTED_PLUS']
assert {('U4', '2'), ('J5', '2'), ('SW1', '2')} == nets['/REGULATOR_VIN']
assert {('U4', '4'), ('J7', '1'), ('SW1', '4')} == nets['/REGULATOR_VOUT']
assert {('J1', '1'), ('Q1', '3'), ('R1', '1'), ('U1', '3'),
        ('J7', '2'), ('SW1', '5')} == nets['/+3V3_AON']
for unused_pin in ['3', '6']:
    assert {('SW1', unused_pin)} in nets.values()
board = pcbnew.LoadBoard('resources/schematics/schematics.kicad_pcb')
actual = {(f.GetReference(),p.GetNumber()):p.GetNetname() for f in board.GetFootprints() for p in f.Pads()}
for net,nodes in nets.items():
    for key in nodes:
        if key in actual: assert actual[key] == net, (key, net, actual[key])
for ref in ['R5', 'C1', 'J5', 'J6', 'J7']:
    assert any(f.GetReference() == ref for f in board.GetFootprints())
assert not any(f.GetReference() == 'R6' for f in board.GetFootprints())
assert not any(f.GetReference() == 'SW1' for f in board.GetFootprints())
print('PASS: sensing, Q2 and master switch nets match; SW1 and LDR are off-board.')

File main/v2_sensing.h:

// Included by main.c: one controller task owns ADC, playback and sleep.
#include "esp_adc/adc_cali.h"
#include "esp_adc/adc_cali_scheme.h"
#include "esp_sleep.h"
#include "esp_system.h"
#include "esp_attr.h"
#include "light_policy.h"

#define PERIPH_EN GPIO_NUM_22
#define LIGHT_POWER GPIO_NUM_14
#define LIGHT_INPUT GPIO_NUM_4
#define LIGHT_ADC_CHANNEL ADC_CHANNEL_4
#define NIGHT_CHECK_SECONDS 30
#define LIGHT_SETTLE_MS 30 // >5 RC constants with 100 nF at ADC node
#define LIGHT_FADE_US 200000LL

static adc_oneshot_unit_handle_t sensing_adc;
static adc_cali_handle_t light_calibration;
static light_policy_t light_policy = {.dark_since = -1};
static bool light_valid;
static int light_mv;
static bool peripherals_on;
static int filtered_volume = -1;
static int64_t last_sense = -1000000;
static int64_t last_light_log = -1000000;
static int64_t last_volume_log;
static RTC_DATA_ATTR unsigned next_track;
static RTC_DATA_ATTR bool saved_night;
static RTC_DATA_ATTR bool armed_for_high;
static RTC_DATA_ATTR uint32_t rtc_cookie;

static void v2_sense(void)
{
    int64_t now = esp_timer_get_time();
    if (now - last_sense < 50000) return;
    last_sense = now;
    int total = 0;
    light_valid = true;
    for (int i = 0; i < 8; ++i) {
        int raw;
        if (adc_oneshot_read(sensing_adc, LIGHT_ADC_CHANNEL, &raw) != ESP_OK) {
            light_valid = false;
            break;
        }
        total += raw;
    }
    if (light_valid && adc_cali_raw_to_voltage(light_calibration, total / 8, &light_mv) != ESP_OK)
        light_valid = false;
    bool previous_night = light_policy.night;
    light_policy_update(&light_policy, light_valid, light_mv, esp_timer_get_time());
    if (previous_night != light_policy.night || now - last_light_log >= 1000000) {
        ESP_LOGI("light", "ADC=%dmV valid=%d night=%d; limits night>%d day<%d mV",
                 light_mv, light_valid, light_policy.night, LIGHT_NIGHT_MV, LIGHT_DAY_MV);
        last_light_log = now;
    }
    if (!peripherals_on) return;
    total = 0;
    for (int i = 0; i < 8; ++i) {
        int raw;
        if (adc_oneshot_read(sensing_adc, VOLUME_ADC_CHANNEL, &raw) != ESP_OK) return;
        total += raw;
    }
    int raw = total / 8;
    filtered_volume = filtered_volume < 0 ? raw : (3 * filtered_volume + raw) / 4;
    int position = filtered_volume <= VOLUME_ADC_MIN ? 0 :
        filtered_volume >= VOLUME_ADC_MAX ? 4095 :
        (filtered_volume - VOLUME_ADC_MIN) * 4095 / (VOLUME_ADC_MAX - VOLUME_ADC_MIN);
    atomic_store(&volume_gain_q15, position * (32768 * VOLUME_PERCENT / 100) / 4095);
    if (ENABLE_VOLUME_DEBUG && now - last_volume_log >= 1000000) {
        ESP_LOGI("volume", "GPIO5 raw=%d filtered=%d gain=%d/%d%%", raw, filtered_volume,
                 atomic_load(&volume_gain_q15) * 100 / 32768, VOLUME_PERCENT);
        last_volume_log = now;
    }
}

static void v2_sensing_init(void)
{
    adc_oneshot_unit_init_cfg_t unit = {.unit_id = ADC_UNIT_1};
    ESP_ERROR_CHECK(adc_oneshot_new_unit(&unit, &sensing_adc));
    adc_oneshot_chan_cfg_t channel = {.bitwidth = ADC_BITWIDTH_12, .atten = ADC_ATTEN_DB_12};
    ESP_ERROR_CHECK(adc_oneshot_config_channel(sensing_adc, LIGHT_ADC_CHANNEL, &channel));
    ESP_ERROR_CHECK(adc_oneshot_config_channel(sensing_adc, VOLUME_ADC_CHANNEL, &channel));
    adc_cali_curve_fitting_config_t cal = {
        .unit_id = ADC_UNIT_1, .chan = LIGHT_ADC_CHANNEL,
        .atten = ADC_ATTEN_DB_12, .bitwidth = ADC_BITWIDTH_12,
    };
    // No uncalibrated raw-to-mV fallback: it would misrepresent resistance thresholds.
    ESP_ERROR_CHECK(adc_cali_create_scheme_curve_fitting(&cal, &light_calibration));
    // Keep the tiny divider powered while awake: no settling delay in audio feed.
    // Both excitation and peripheral supply are held LOW throughout deep sleep.
    ESP_ERROR_CHECK(gpio_set_level(LIGHT_POWER, 1));
    vTaskDelay(pdMS_TO_TICKS(LIGHT_SETTLE_MS));
}

static void v2_safe_interfaces(void)
{
    const gpio_num_t pins[] = {AUDIO_DIN, AUDIO_BCLK, AUDIO_LRC,
                               SD_CS, SD_MOSI, SD_CLK, SD_MISO, GPIO_NUM_5};
    for (unsigned i = 0; i < sizeof(pins)/sizeof(pins[0]); ++i) {
        ESP_ERROR_CHECK(gpio_reset_pin(pins[i]));
        ESP_ERROR_CHECK(gpio_set_direction(pins[i], GPIO_MODE_INPUT));
        ESP_ERROR_CHECK(gpio_set_pull_mode(pins[i], GPIO_FLOATING));
    }
}

static void v2_sleep(bool suppress_motion)
{
    v2_safe_interfaces();
    ESP_ERROR_CHECK(gpio_set_level(PERIPH_EN, 0));
    ESP_ERROR_CHECK(gpio_set_level(LIGHT_POWER, 0));
    ESP_ERROR_CHECK(gpio_hold_en(PERIPH_EN));
    ESP_ERROR_CHECK(gpio_hold_en(LIGHT_POWER));
    // ESP32-C6 supports per-pad deep-sleep hold directly via gpio_hold_en.
    saved_night = light_policy.night;
    rtc_cookie = 0x42425832;
    ESP_ERROR_CHECK(esp_sleep_disable_wakeup_source(ESP_SLEEP_WAKEUP_ALL));
    ESP_ERROR_CHECK(esp_sleep_enable_timer_wakeup(NIGHT_CHECK_SECONDS * 1000000ULL));
    armed_for_high = false;
    if (!suppress_motion) {
        // HIGH sensor: wait for LOW first. LOW sensor: arm the next HIGH.
        armed_for_high = gpio_get_level(PIR_INPUT) == 0;
        ESP_ERROR_CHECK(esp_sleep_enable_ext1_wakeup_io(1ULL << PIR_INPUT,
            armed_for_high ? ESP_EXT1_WAKEUP_ANY_HIGH : ESP_EXT1_WAKEUP_ANY_LOW));
    }
    ESP_LOGI(TAG, "Deep sleep: night=%d motion=%s next_track=%u",
             saved_night, suppress_motion ? "disabled" : armed_for_high ? "HIGH" : "LOW rearm",
             next_track + 1);
    esp_deep_sleep_start();
}
